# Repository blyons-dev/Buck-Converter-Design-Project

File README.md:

# Buck Converter Design Project
This project focuses on the design and implementation of a DC-DC Buck Converter system controlled by an Arduino Nano. The system dynamically adjusts the duty cycle of a PWM signal to regulate and stabilize the output voltage under varying conditions.
## Overview
The goal of this project is to develop a reliable and flexible buck converter that demonstrates closed-loop control using a microcontroller. By leveraging the Arduino Nano, the system can monitor output voltage and automatically adjust the switching behavior to maintain a desired voltage level. The system can also optionally be controlled using an external function generator.
## Features
- Closed-loop voltage regulation using PWM control
- Arduino Nano-based control system
- Adjustable duty cycle for output voltage tuning
- Modular design for testing and iteration
- Suitable for control algorithm development and experimentation
## System Architecture
The system consists of three main components:
- Power Stage: Includes the switching element, diode, inductor, and capacitor forming the buck converter
- Control System: Arduino Nano generating PWM and adjusting duty cycle
- Feedback Network: Voltage sensing circuit used for regulation
## Schematic Diagram

## PCB Layout (Mimics layout of perfboard)

## Circuit Prototype

## How It Works
1. The Arduino Nano generates a PWM signal.
2. The duty cycle of the PWM signal controls the average output voltage of the buck converter.
3. The output voltage is measured through a feedback circuit.
4. The Arduino adjusts the duty cycle in real time to maintain the desired output voltage.
## Applications
- Power supply design
- Embedded control systems
- Educational demonstrations of DC-DC conversion
- Development of control algorithms for power electronics

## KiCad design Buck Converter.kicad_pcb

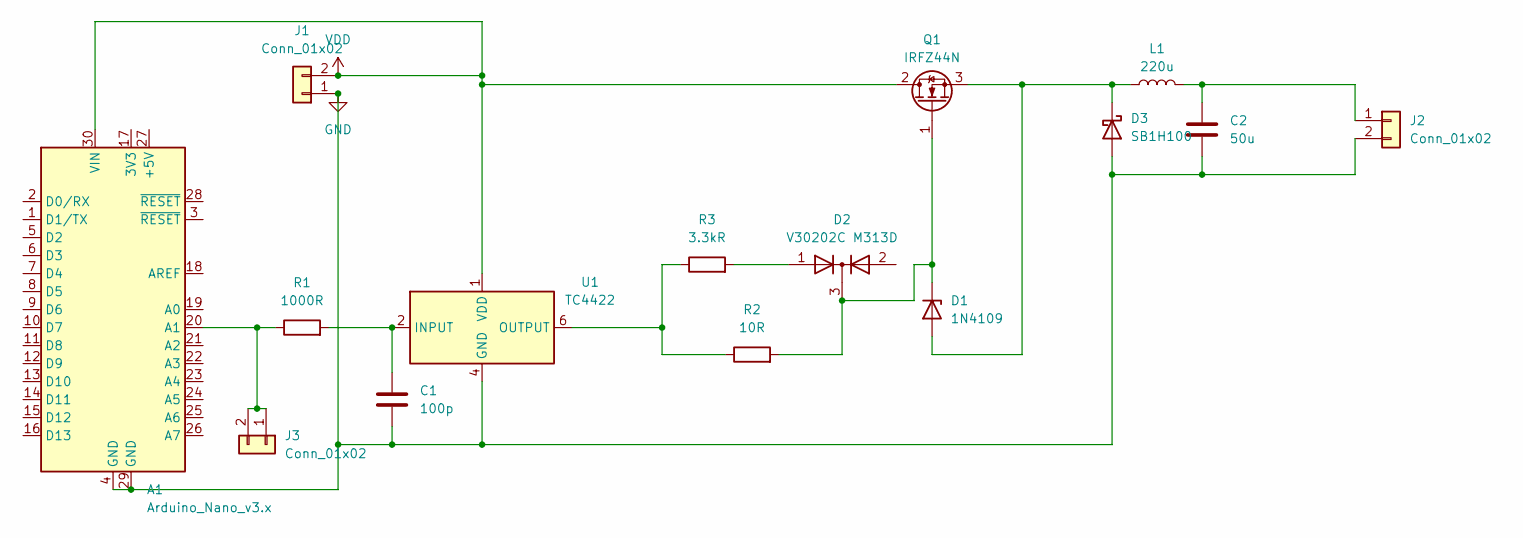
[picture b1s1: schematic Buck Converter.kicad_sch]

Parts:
A1: Arduino_Nano_v3.x; Arduino_Nano
C1: 100p; C_Radial_D10.0mm_H12.5mm_P5.00mm
C2: 50u; C_Radial_D10.0mm_H12.5mm_P5.00mm
D1: 1N4109; D_DO-41_SOD81_P10.16mm_Horizontal
D2: V30202C M313D; TO-220-3_Vertical
D3: SB1H100; D_DO-41_SOD81_P10.16mm_Horizontal
J1, J2, J3: Conn_01x02; PinSocket_1x02_P2.54mm_Vertical
L1: 220u; L_Wurth_WE-HCFT-2012_LeadDiameter1.2mm
Q1: IRFZ44N; TO-220-3_Vertical
R1: 1000R; R_Axial_DIN0411_L9.9mm_D3.6mm_P7.62mm_Vertical
R2: 10R; R_Axial_DIN0411_L9.9mm_D3.6mm_P7.62mm_Vertical
R3: 3.3kR; R_Axial_DIN0411_L9.9mm_D3.6mm_P7.62mm_Vertical
U1: TC4422; DIP-8_W7.62mm

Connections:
GND: A1.4 (GND), A1.29 (GND), C1.2, C2.2, D3.2 (A), J1.1, J2.2, U1.4 (GND), U1.5 (GND)
unnamed: A1.20 (A1), J3.1, J3.2, R1.1
unnamed: D1.2 (A), D3.1 (K), L1.1, Q1.3 (S)
unnamed: D1.1 (K), D2.3 (K), Q1.1 (G), R2.2
unnamed: D2.1 (A), R3.2
unnamed: C2.1, J2.1, L1.2
unnamed: R2.1, R3.1, U1.6 (OUTPUT), U1.7 (OUTPUT)
unnamed: C1.1, R1.2, U1.2 (INPUT)
VDD: A1.30 (VIN), J1.2, Q1.2 (D), U1.1 (VDD), U1.8 (VDD)

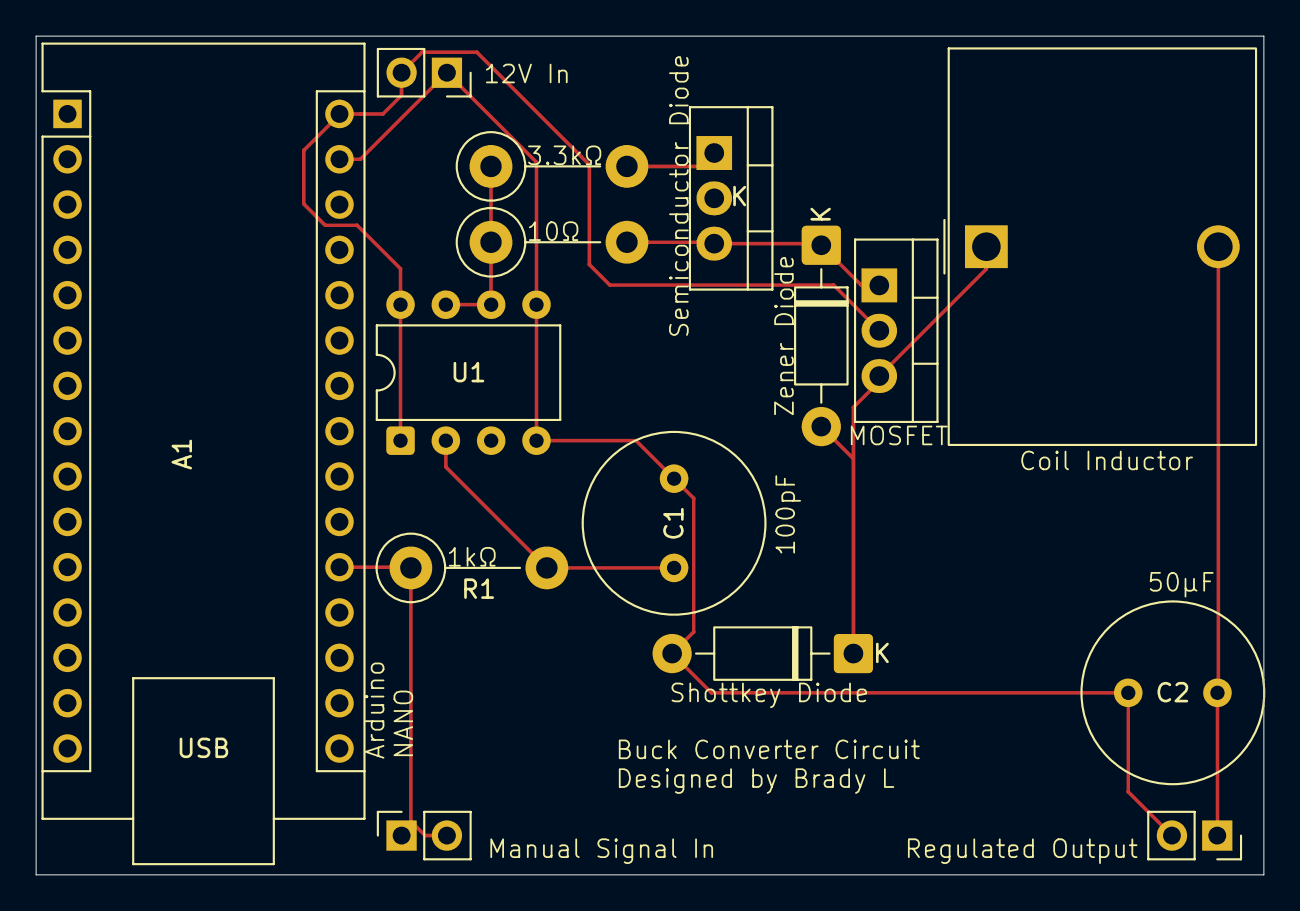
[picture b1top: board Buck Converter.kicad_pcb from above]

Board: 2 copper layers, 68.8 x 47.0 mm, 15 parts (0 on the bottom side), 9 nets.

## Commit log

2026-03-25 Created Layout
2026-03-25 Revise README with detailed project information
    Expanded project description and added sections on features, system architecture, schematic diagram, PCB layout, operation, applications, and KiCad setup instructions.
2026-03-25 Add Git plugin installation step for KiCad
    Added instructions to install the Git plugin for KiCad.
2026-04-27 Revise README with PCB layout and circuit prototype
    Updated README to include new PCB layout section and circuit prototype details. Removed KiCad setup instructions.
2026-04-29 Replace schematic diagram image in README
    Updated schematic diagram image in README.
